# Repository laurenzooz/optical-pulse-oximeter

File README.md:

### TODO:

* Two ways to measure the pulse:
	* Perform FFT, find the highest amplitude frequency, calculate pulse from that	
	* Measure the time between the peaks, few peaks at a time, calculate the average of the durations between peaks	

	test

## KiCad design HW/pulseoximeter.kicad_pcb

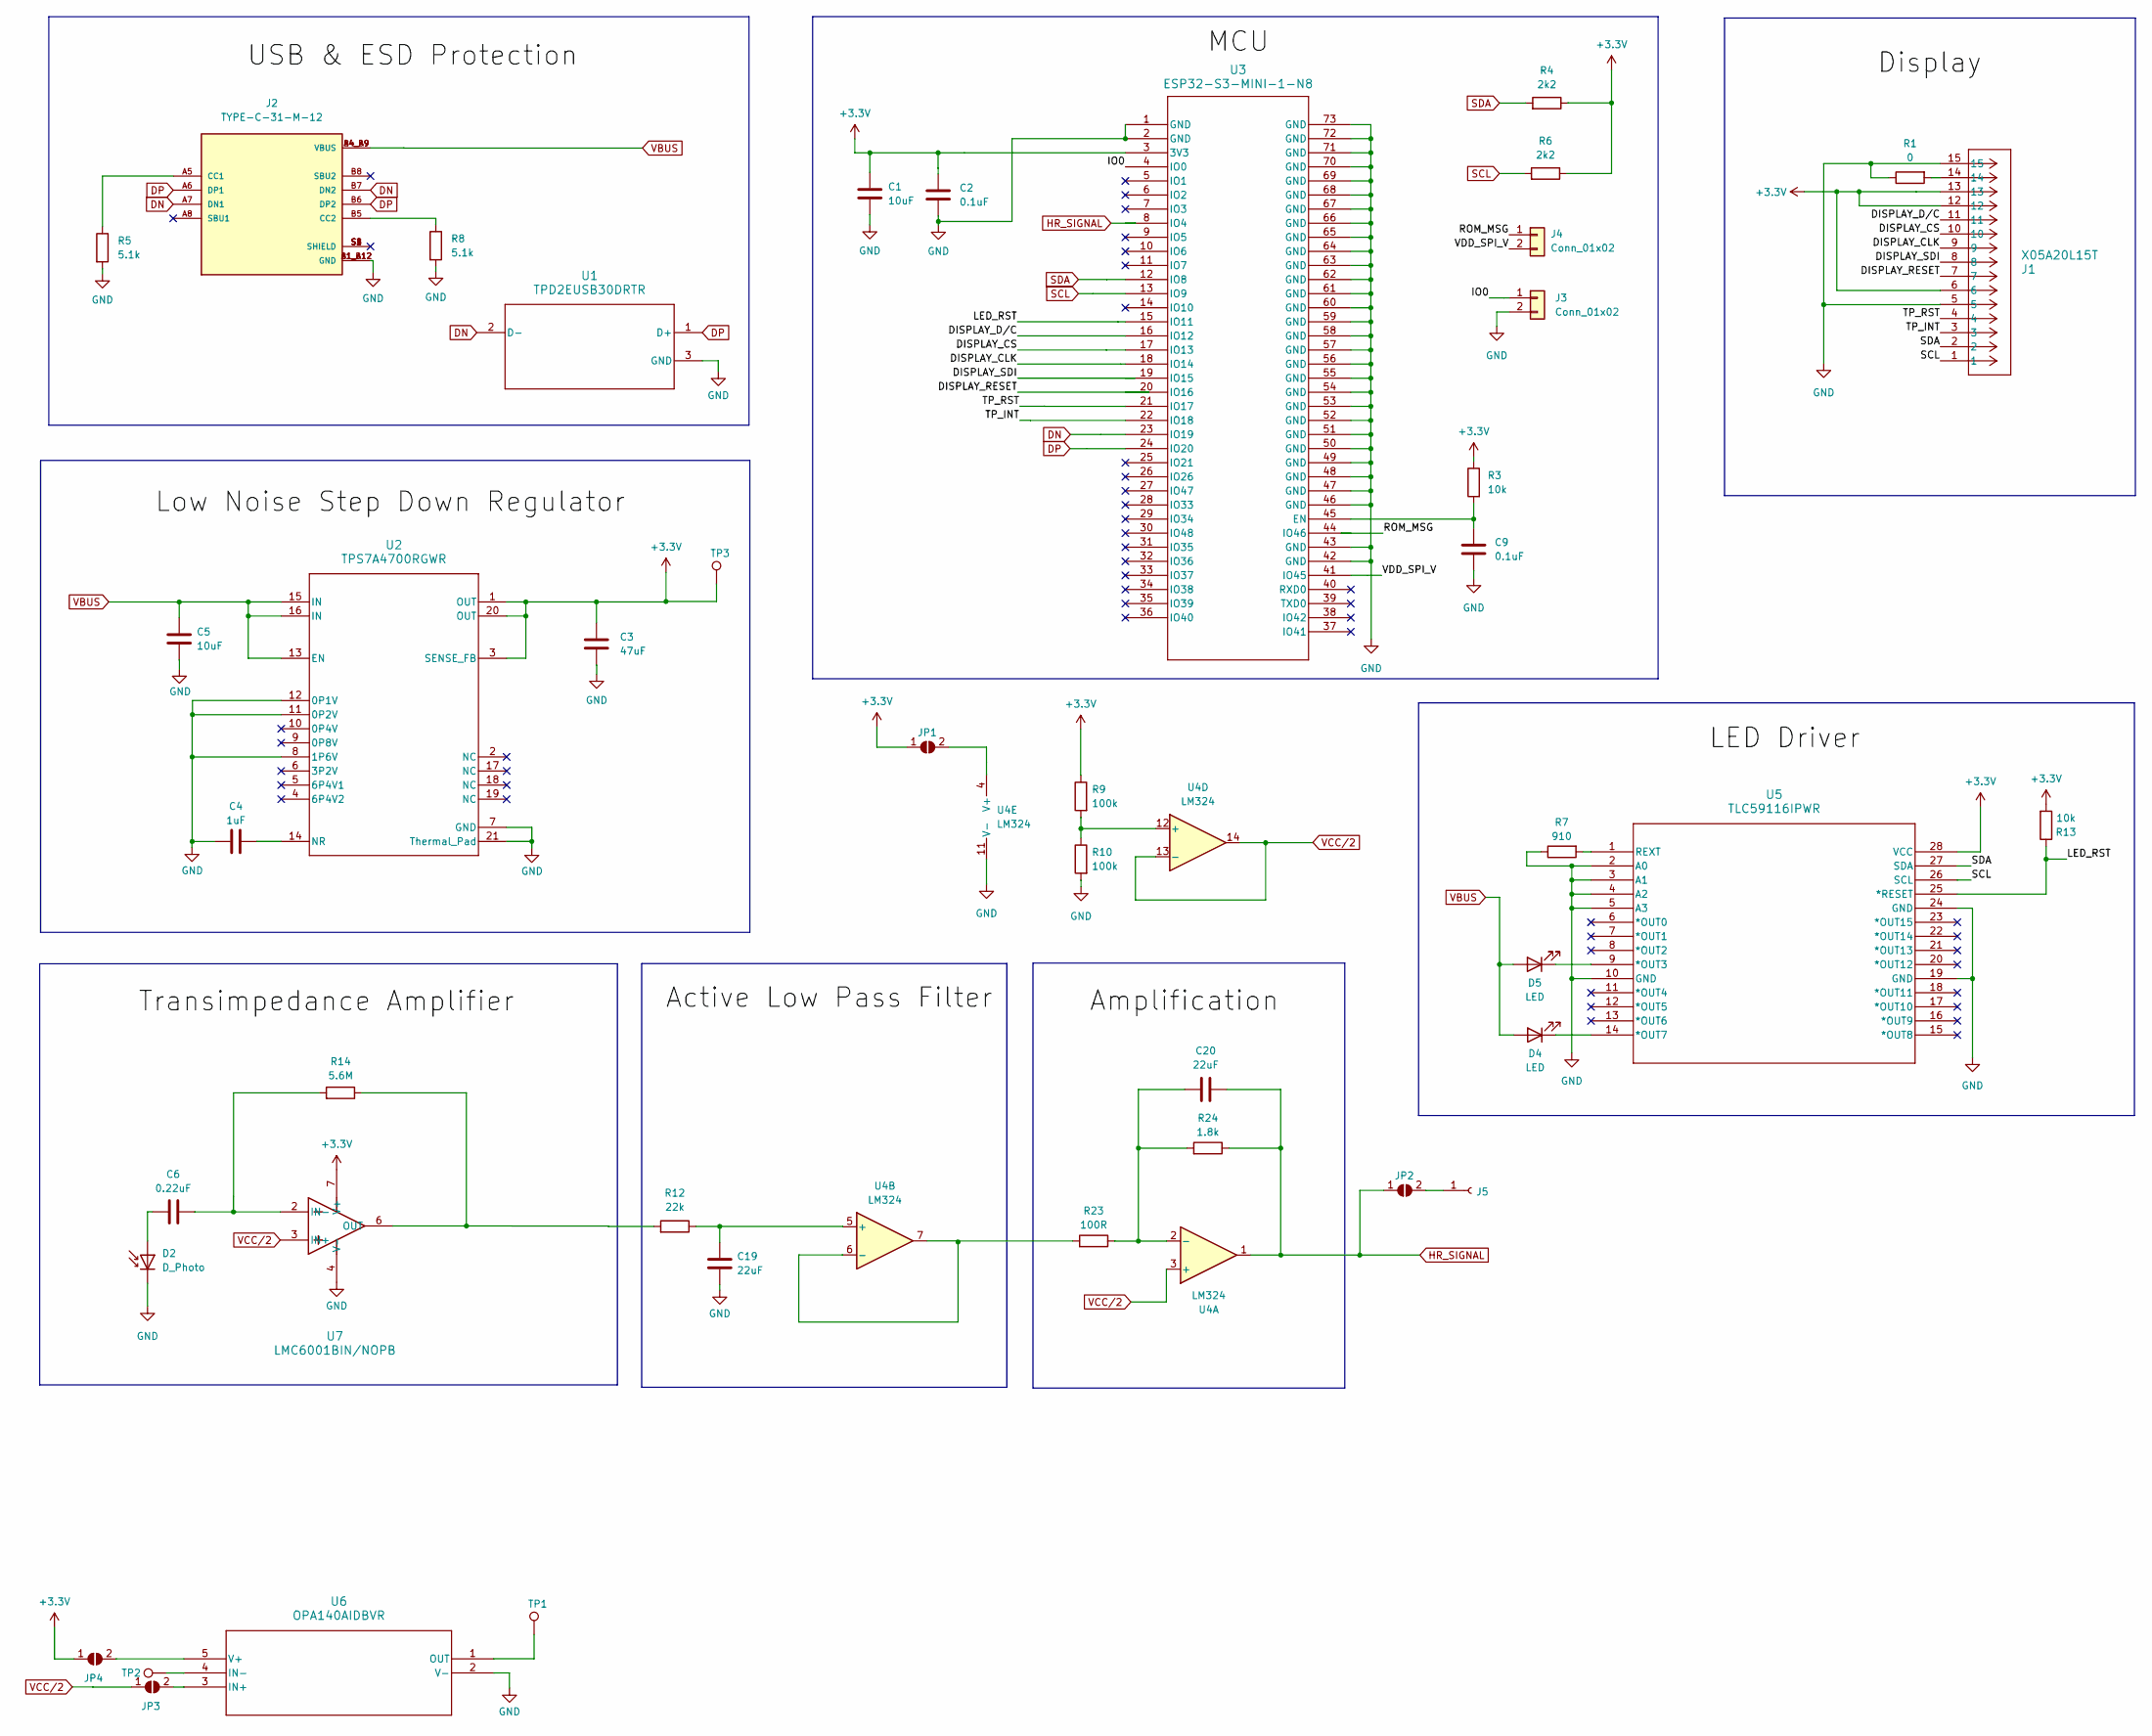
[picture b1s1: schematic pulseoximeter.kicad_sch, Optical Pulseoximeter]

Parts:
C1: 10uF; C_0603_1608Metric
C2, C9: 0.1uF; C_0603_1608Metric
C3: 47uF; C_0603_1608Metric
C4: 1uF; C_0402_1005Metric
C5: 10uF; C_0402_1005Metric
C6: 0.22uF; C_0603_1608Metric
C19, C20: 22uF; C_0603_1608Metric
D2: D_Photo; LED_D3.0mm
D4, D5: LED; LED_D3.0mm
J1: X05A20L15T; CONN_X05A20L15T_XKB
J2: TYPE-C-31-M-12; PARTREV 2020.12.08
J3, J4: Conn_01x02; PinHeader_1x02_P2.54mm_Vertical
J5: Conn_01x01_Socket; PinHeader_1x01_P2.54mm_Vertical
JP1, JP2, JP3, JP4: SolderJumper_2_Open; SolderJumper-2_P1.3mm_Open_RoundedPad1.0x1.5mm
R1: 0; R_0603_1608Metric
R3, R13: 10k; R_0603_1608Metric
R4, R6: 2k2; R_0603_1608Metric
R5, R8: 5.1k; R_0402_1005Metric
R7: 910; R_0603_1608Metric
R9, R10: 100k; R_0603_1608Metric
R12: 22k; R_0805_2012Metric
R14: 5.6M; R_0805_2012Metric
R23: 100R; R_0603_1608Metric
R24: 1.8k; R_0603_1608Metric
TP1, TP2, TP3: TestPoint; TestPoint_Pad_D2.0mm
U1: TPD2EUSB30DRTR; DRT0003A
U2: TPS7A4700RGWR; RGW0020A-IPC_A
U3: ESP32-S3-MINI-1-N8; ESP32-S3-MINI-1_EXP
U4: LM324; D14
U5: TLC59116IPWR; PW28
U6: OPA140AIDBVR; DBV5
U7: LMC6001BIN/NOPB; DIP794W45P254L959H508Q8

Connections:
+3.3V: C1.1, C2.1, C3.1, J1.6, J1.12, J1.13, JP1.1 (A), JP4.1 (A), R3.1, R4.1, R6.1, R9.1, R13.2, TP3.1, U2.1 (OUT), U2.3 (SENSE_FB), U2.20 (OUT), U3.3 (3V3), U5.28 (VCC), U7.7 (V+)
/DISPLAY_CLK: J1.9, U3.18 (IO14)
/DISPLAY_CS: J1.10, U3.17 (IO13)
/DISPLAY_D/C: J1.11, U3.16 (IO12)
/DISPLAY_RESET: J1.7, U3.20 (IO16)
/DISPLAY_SDI: J1.8, U3.19 (IO15)
/IO0: J3.1, U3.4 (IO0)
/LED_RST: R13.1, U3.15 (IO11), U5.25 (*RESET)
/ROM_MSG: J4.1, U3.44 (IO46)
/TP_INT: J1.3, U3.22 (IO18)
/TP_RST: J1.4, U3.21 (IO17)
/VDD_SPI_V: J4.2, U3.41 (IO45)
DN: J2.A7 (DN1), J2.B7 (DN2), U1.2 (D-), U3.23 (IO19)
DP: J2.A6 (DP1), J2.B6 (DP2), U1.1 (D+), U3.24 (IO20)
GND: C1.2, C2.2, C3.2, C4.1, C5.2, C9.2, C19.2, D2.1 (K), J1.5, J1.15, J2.A1_B12 (GND), J2.B1_A12 (GND), J3.2, R1.1, R5.2, R7.1, R8.2, R10.2, U1.3 (GND), U2.7 (GND), U2.8 (1P6V), U2.11 (0P2V), U2.12 (0P1V), U2.21 (Thermal_Pad), U3.1 (GND), U3.2 (GND), U3.42 (GND), U3.43 (GND), U3.46 (GND), U3.47 (GND), U3.48 (GND), U3.49 (GND), U3.50 (GND), U3.51 (GND), U3.52 (GND), U3.53 (GND), U3.54 (GND), U3.55 (GND), U3.56 (GND), U3.57 (GND), U3.58 (GND), U3.59 (GND), U3.60 (GND), U3.61 (GND), U3.62 (GND), U3.63 (GND), U3.64 (GND), U3.65 (GND), U3.66 (GND), U3.67 (GND), U3.68 (GND), U3.69 (GND), U3.70 (GND), U3.71 (GND), U3.72 (GND), U3.73 (GND), U4.11 (V-), U5.2 (A0), U5.3 (A1), U5.4 (A2), U5.5 (A3), U5.10 (GND), U5.19 (GND), U5.24 (GND), U6.2 (V-), U7.4 (V-)
HR_SIGNAL: C20.1, JP2.1 (A), R24.1, U3.8 (IO4), U4.1
unnamed: C6.1, D2.2 (A)
unnamed: D4.1 (K), U5.14 (*OUT7)
unnamed: D5.1 (K), U5.9 (*OUT3)
unnamed: J1.14, R1.2
unnamed: J2.A5 (CC1), R5.1
unnamed: J2.B5 (CC2), R8.1
unnamed: J5.1, JP2.2 (B)
unnamed: JP1.2 (B), U4.4 (V+)
unnamed: JP3.2 (B), U6.3 (IN+)
unnamed: JP4.2 (B), U6.5 (V+)
unnamed: C4.2, U2.14 (NR)
unnamed: C9.1, R3.2, U3.45 (EN)
unnamed: C20.2, R23.1, R24.2, U4.2 (-)
unnamed: C19.1, R12.1, U4.5 (+)
unnamed: R23.2, U4.6 (-), U4.7
unnamed: R9.2, R10.1, U4.12 (+)
unnamed: R7.2, U5.1 (REXT)
unnamed: TP2.1, U6.4 (IN-)
unnamed: TP1.1, U6.1 (OUT)
unnamed: C6.2, R14.2, U7.2 (IN-)
unnamed: R12.2, R14.1, U7.6 (OUT)
SCL: J1.1, R6.2, U3.13 (IO9), U5.26 (SCL)
SDA: J1.2, R4.2, U3.12 (IO8), U5.27 (SDA)
VBUS: C5.1, D4.2 (A), D5.2 (A), J2.A4_B9 (VBUS), J2.B4_A9 (VBUS), U2.13 (EN), U2.15 (IN), U2.16 (IN)
VCC/2: JP3.1 (A), U4.3 (+), U4.13 (-), U4.14, U7.3 (IN+)

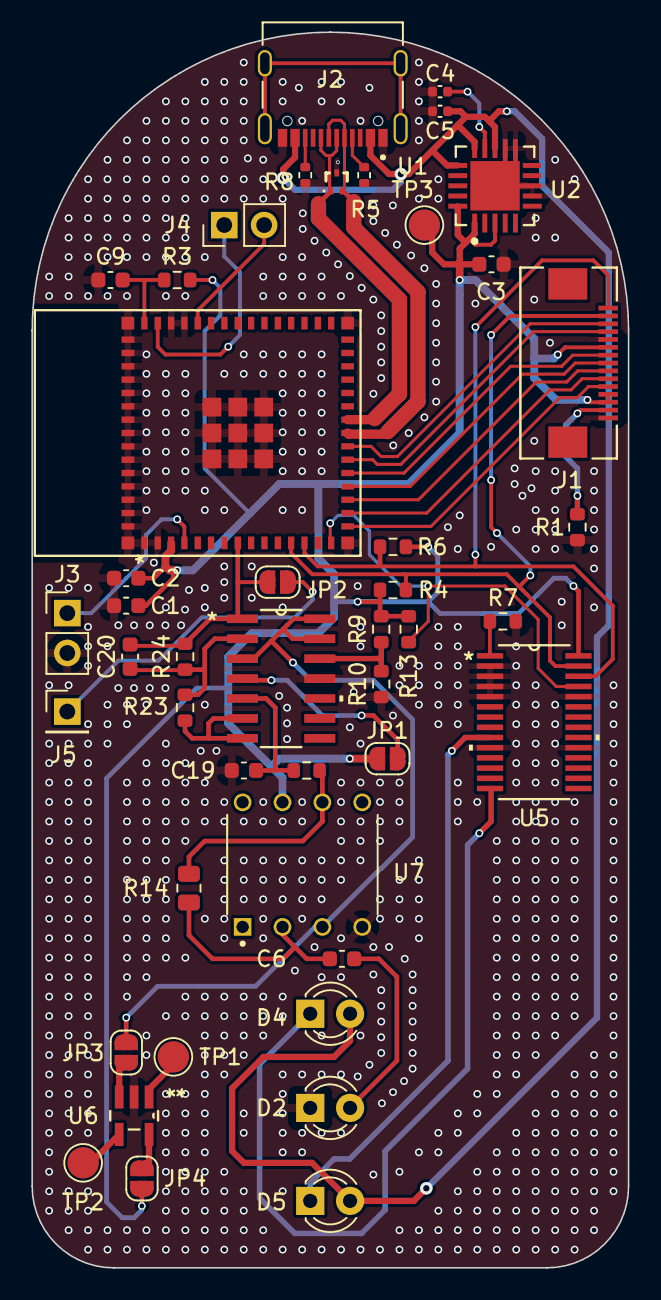
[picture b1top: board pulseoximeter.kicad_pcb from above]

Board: 2 copper layers, 38.0 x 78.7 mm, 45 parts (0 on the bottom side), 41 nets.

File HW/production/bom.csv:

Designator,Footprint,Quantity,Value,LCSC Part #
C1,0603,1,10uF,
"C19, C20",0603,2,22uF,
"C2, C9",0603,2,0.1uF,
C3,0603,1,47uF,
C4,0402,1,1uF,
C5,0402,1,10uF,
C6,0603,1,0.22uF,
J1,CONN_X05A20L15T_XKB,1,X05A20L15T,
J2,TYPE-C-31-M-12,1,TYPE-C-31-M-12,
R1,0603,1,0,
"R10, R9",0603,2,100k,
R12,0603,1,22k,
"R13, R3",0603,2,10k,
R14,0805,1,5.6M,
R23,0603,1,100R,
R24,0603,1,1.8k,
"R4, R6",0603,2,2k2,
"R5, R8",0402,2,5.1k,
R7,0603,1,910,
U1,DRT0003A,1,TPD2EUSB30DRTR,
U2,RGW0020A-IPC_A,1,TPS7A4700RGWR,
U3,ESP32-S3-MINI-1_EXP,1,ESP32-S3-MINI-1-N8,
U4,D14,1,LM324,
U5,PW28,1,TLC59116IPWR,
U6,DBV5,1,OPA140AIDBVR,

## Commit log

2024-10-28 readme added
2024-10-28 added code template for signal processsing
2024-10-28 Add TODO
2024-10-28 Added sample FFT made with chatgpt
2024-10-28 Update code to calculate and print the pulse
2024-10-28 testi1
2024-10-28 removed lol
2024-10-28 edited readme
2024-10-28 added datasets
2024-10-30 current code
2024-11-01 BLE support
2024-11-01 Added file reading
2024-11-01 Works with file reading
2024-11-01 not sending incorrect pulses
2024-11-02 Update according the python tests
2024-11-03 restore
2024-11-03 Add tester
2024-11-03 Receive data over serial, find highest peak, calculate pulse from that
2024-11-03 setup fft
2024-11-03 Remove commented code
2024-11-03 fix incorrect variable call
2024-11-03 update tester
2024-11-03 Add comment
2024-11-03 Add test data
2024-11-03 update port
2024-11-03 fix incorret variable names
2024-11-03 modify
2024-11-03 fix the freq
2024-11-03 update magnitude finding
2024-11-03 fix the data so it syncs when repeating
2024-11-03 repeat
2024-11-03 change limits, no longer print, only bluetooth
2024-11-03 Send single datapoints over bluetooth
2024-11-03 serial print bpm only
2024-11-03 added schematic v1
2024-11-05 Store three values and find the median
2024-11-05 fix typos
2024-11-05 change port
2024-11-05 Moving HW to seperate repository
2024-11-06 clean serial output
2024-11-06 add variable for sampling frequency, test with 1ms interval
2024-11-06 sampling freq to float
2024-11-06 test the welch windowing function
2024-11-06 correct the wait time
2024-11-06 chatgpt weighed frequency calculation test
2024-11-06 slightly lower delay
2024-11-06 reduce points per interval
2024-11-08 ver2
2024-11-08 refine data
2024-11-09 Add peak detection library
2024-11-09 update to peak detection
2024-11-09 clean old code, only calculate average when enough values are measured
2024-11-10 Update the char uuid
2024-11-11 Send raw sensor data as well
2024-11-19 Tune parameters
2024-11-19 add submodules
2024-11-29 display works
2024-12-01 implemented dynamic chart y-axis scaling
